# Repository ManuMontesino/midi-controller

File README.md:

# midi-controller

Controlador USB-MIDI + HID basado en RP2040: 8 encoders con anillo de LEDs, 8 teclas mecánicas con LED RGB, salida MIDI TRS y header de expansión.

> **Estado: Rev. 1, diseño terminado y listo para fabricar.** Pasa ERC y DRC sin errores, tiene archivos de producción para JLCPCB y la revisión de pinouts contra las hojas de datos está hecha. Todavía no se fabricó: el arranque de la placa (bring-up) y el firmware son los próximos pasos.

---

## Características

- **RP2040 como chip suelto** (no un módulo Pico): flash QSPI W25Q16 de 2 MB, cristal de 12 MHz, USB-C con protección ESD y polyfuse.
- **32 entradas** leídas con 4× 74HC165 en cadena: 8 encoders EC11 (A, B y pulsador) y 8 teclas MX.
- **144 LEDs** manejados por un IS31FL3741A por I2C: 8 anillos de 15 LEDs y 8 LEDs RGB debajo de las teclas, con PWM independiente para cada LED.
- **MIDI TRS (Type A)** a 3.3 V, además de USB-MIDI.
- **Header de expansión** con 6 GPIO, 3 entradas ADC, 3V3 y GND, para variantes sin rediseñar la placa base.
- **Debug:** header SWD y botones BOOTSEL y RESET.

## Hardware

```
USB-C ──► ESD + polyfuse ──► LDO 3.3V ──┬──► RP2040 + flash QSPI + cristal 12 MHz
                                        │       ├─ SPI ──► 4× 74HC165 ◄── 8 encoders + 8 teclas
                                        │       ├─ I2C ──► IS31FL3741A ──► 8 anillos + 8 RGB
                                        │       ├─ UART ─► jack TRS (MIDI out)
                                        │       └─ GPIO / ADC ──► header de expansión
                                        └──► +5V ──► alimentación de la matriz de LEDs
```

| | |
|---|---|
| Herramienta | KiCad 9, esquemático jerárquico de 6 hojas |
| PCB | 4 capas (señal / GND / 3V3 / señal), ~170 × 110 mm, 1.6 mm |
| Reglas | Pista y separación de 0.2 mm (0.15 mm en el fan-out del RP2040 y del IS31) |
| Componentes | 204 piezas SMD y THT ensamblables en JLCPCB (Economic PCBA, una sola cara) |
| Costo del prototipo | ~USD 150 por 5 PCB, 2 de ellas ensambladas, sin envío ni impuestos |

### Decisiones de diseño

Cada decisión está explicada en detalle en [las notas de diseño](docs/notas-de-diseno.md). Las principales:

- **Registros de desplazamiento en lugar de GPIO directos.** 32 entradas con solo 3 pines. Cada chip se agrupa por zona de la placa y no por tipo de señal, para acortar el ruteo.
- **Matriz de LEDs a 5 V con lógica a 3.3 V.** Un LED blanco (~3 V) más la caída del driver (hasta 1.35 V) necesita unos 4.35 V, así que a 3.3 V no prendería. Alimentarla desde 5 V además evita que la corriente de los LEDs pase por el LDO. El IS31 acepta lógica de 3.3 V, así que no hace falta convertir niveles.
- **USB-C hecho bien.** Una resistencia de 5.1k en cada pin CC, para que funcione con cables C-a-C. ESD con un USBLC6 de tipo "flow-through" pegado al conector y resistencias de 27 Ω en D+/D− junto al RP2040.
- **BOOTSEL sin pin dedicado.** El botón tira QSPI_SS a GND a través de 1k: la ROM lo lee al arrancar y el RP2040 todavía puede manejar la línea.
- **Estados seguros al arrancar.** SDB del IS31 tiene un pull-down, así que los LEDs quedan apagados hasta que el firmware los habilita.
- **Ruteo.** Desacoples pegados a cada pin de alimentación, par USB ruteado junto y plano de GND continuo en In1.

## Imágenes

| Vista superior | Cobre: F.Cu (rojo) y B.Cu (azul) |
|---|---|
|  |  |

| Plano In1 (GND) | Plano In2 (3V3) |
|---|---|
|  |  |

Esquemático completo: [docs/esquematico-rev1.pdf](docs/esquematico-rev1.pdf)

## Verificación

- **ERC:** 0 errores. **DRC:** 0 violaciones, 0 pads sin conectar y placa en paridad con el esquemático.
- **Revisión manual de pinouts contra las hojas de datos:** USB-C, USBLC6, AP2112K, RP2040 (alimentación, cristal y QSPI), W25Q16, 74HC165 e IS31FL3741A.
- **Disponibilidad de componentes en JLCPCB/LCSC:** las piezas sin stock se reemplazaron por equivalentes o se marcaron para soldar a mano.

## Fabricación

Los archivos de producción para JLCPCB están en [`hardware/midi-controller/fab/jlcpcb/`](hardware/midi-controller/fab/jlcpcb/): Gerbers y taladros en un zip, BOM con códigos LCSC y CPL de posiciones.

Se sueldan a mano: el jack MIDI (J2), las teclas MX, y los headers SWD y de expansión.

## Próximos pasos

1. **Bring-up:** medir los rieles de alimentación (hay test points en +5V, +3V3 y +1V1), comprobar que el RP2040 enumera en modo BOOTSEL y hacer un escaneo I2C (el IS31 debe responder en 0x30).
2. **Firmware** (Pico SDK + TinyUSB): lectura de entradas en el core 1, USB-MIDI/HID y LEDs en el core 0. Las notas para el firmware están en la sección 8 de [las notas de diseño](docs/notas-de-diseno.md).
3. **Configurador web** con Web MIDI y SysEx.

La especificación completa está en [`controlador-midi-spec.md`](controlador-midi-spec.md).

## Estructura

| Carpeta | Contenido |
|---|---|
| `hardware/midi-controller/` | Proyecto KiCad 9 (esquemático jerárquico + PCB de 4 capas) |
| `hardware/midi-controller/fab/jlcpcb/` | Gerbers, BOM y CPL para JLCPCB |
| `docs/` | Notas de diseño, esquemático en PDF e imágenes |
| `firmware/` | Firmware (por empezar) |
| `configurator/` | Configurador web (por empezar) |

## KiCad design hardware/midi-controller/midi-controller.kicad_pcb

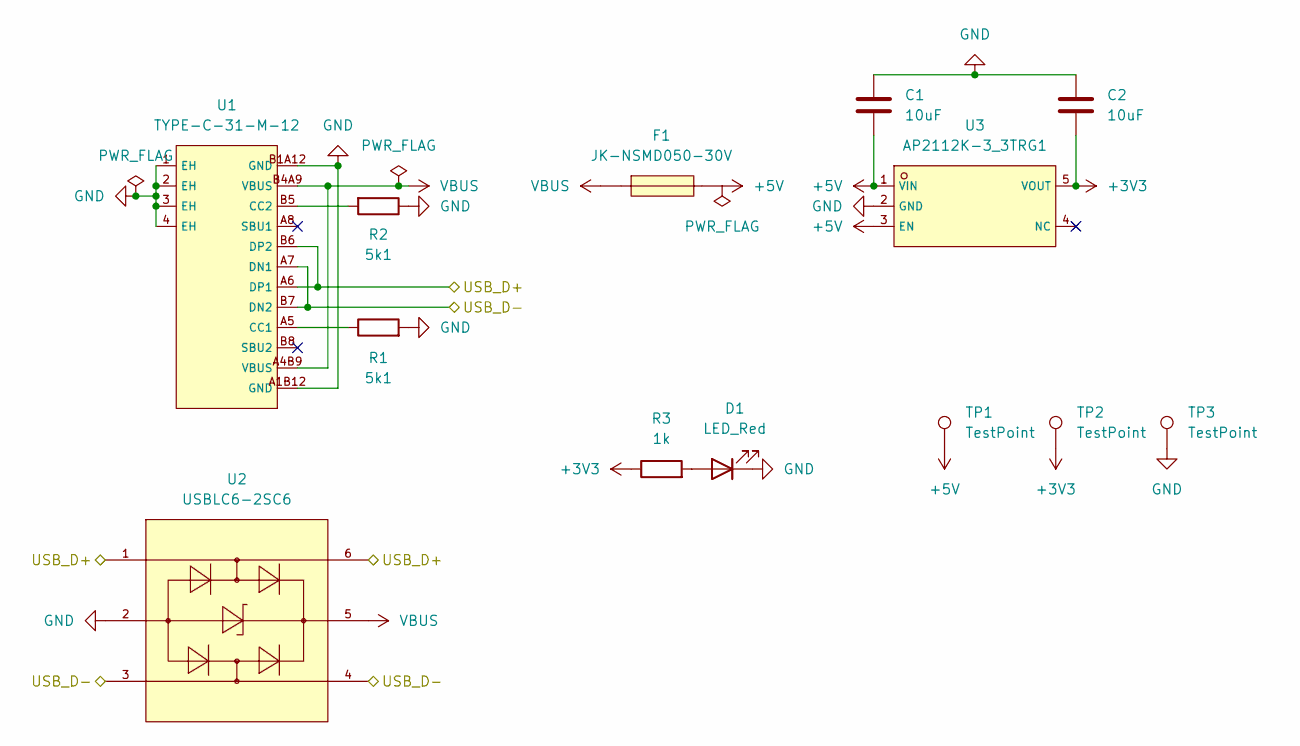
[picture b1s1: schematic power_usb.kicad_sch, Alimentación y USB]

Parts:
C1, C2: 10uF; C_0805_2012Metric; LCSC C15850
D1: LED_Red; LED_0603_1608Metric; LCSC C2286
F1: JK-NSMD050-30V; F1206; LCSC C720075
R1, R2: 5k1; R_0402_1005Metric; LCSC C25905
R3: 1k; R_0402_1005Metric; LCSC C11702
TP1, TP2, TP3: TestPoint; TestPoint_Pad_D1.5mm
U1: TYPE-C-31-M-12; USB-C_SMD-TYPE-C-31-M-12_1; LCSC C165948
U2: USBLC6-2SC6; SOT-23-6_L2.9-W1.6-P0.95-LS2.8-BL; LCSC C7519
U3: AP2112K-3_3TRG1; SOT-25-5_L2.9-W1.6-P0.95-LS2.8-BL; LCSC C51118

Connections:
+3V3: C2.2, R3.1, TP2.1, U3.5 (VOUT); also elsewhere on the board
+5V: C1.2, F1.2, TP1.1, U3.1 (VIN), U3.3 (EN); also elsewhere on the board
/Alimentación y USB/USB_D+: U1.A6 (DP1), U1.B6 (DP2), U2.1 (I/O1), U2.6 (I/O1); also elsewhere on the board
/Alimentación y USB/USB_D-: U1.A7 (DN1), U1.B7 (DN2), U2.3 (I/O2), U2.4 (I/O2); also elsewhere on the board
GND: C1.1, C2.1, D1.1 (K), R1.2, R2.1, TP3.1, U1.1 (EH), U1.2 (EH), U1.3 (EH), U1.4 (EH), U1.A1B12 (GND), U1.B1A12 (GND), U2.2 (GND), U3.2 (GND); also elsewhere on the board
unnamed: D1.2 (A), R3.2
unnamed: R1.1, U1.A5 (CC1)
unnamed: R2.2, U1.B5 (CC2)
VBUS: F1.1, U1.A4B9 (VBUS), U1.B4A9 (VBUS), U2.5 (VBUS)

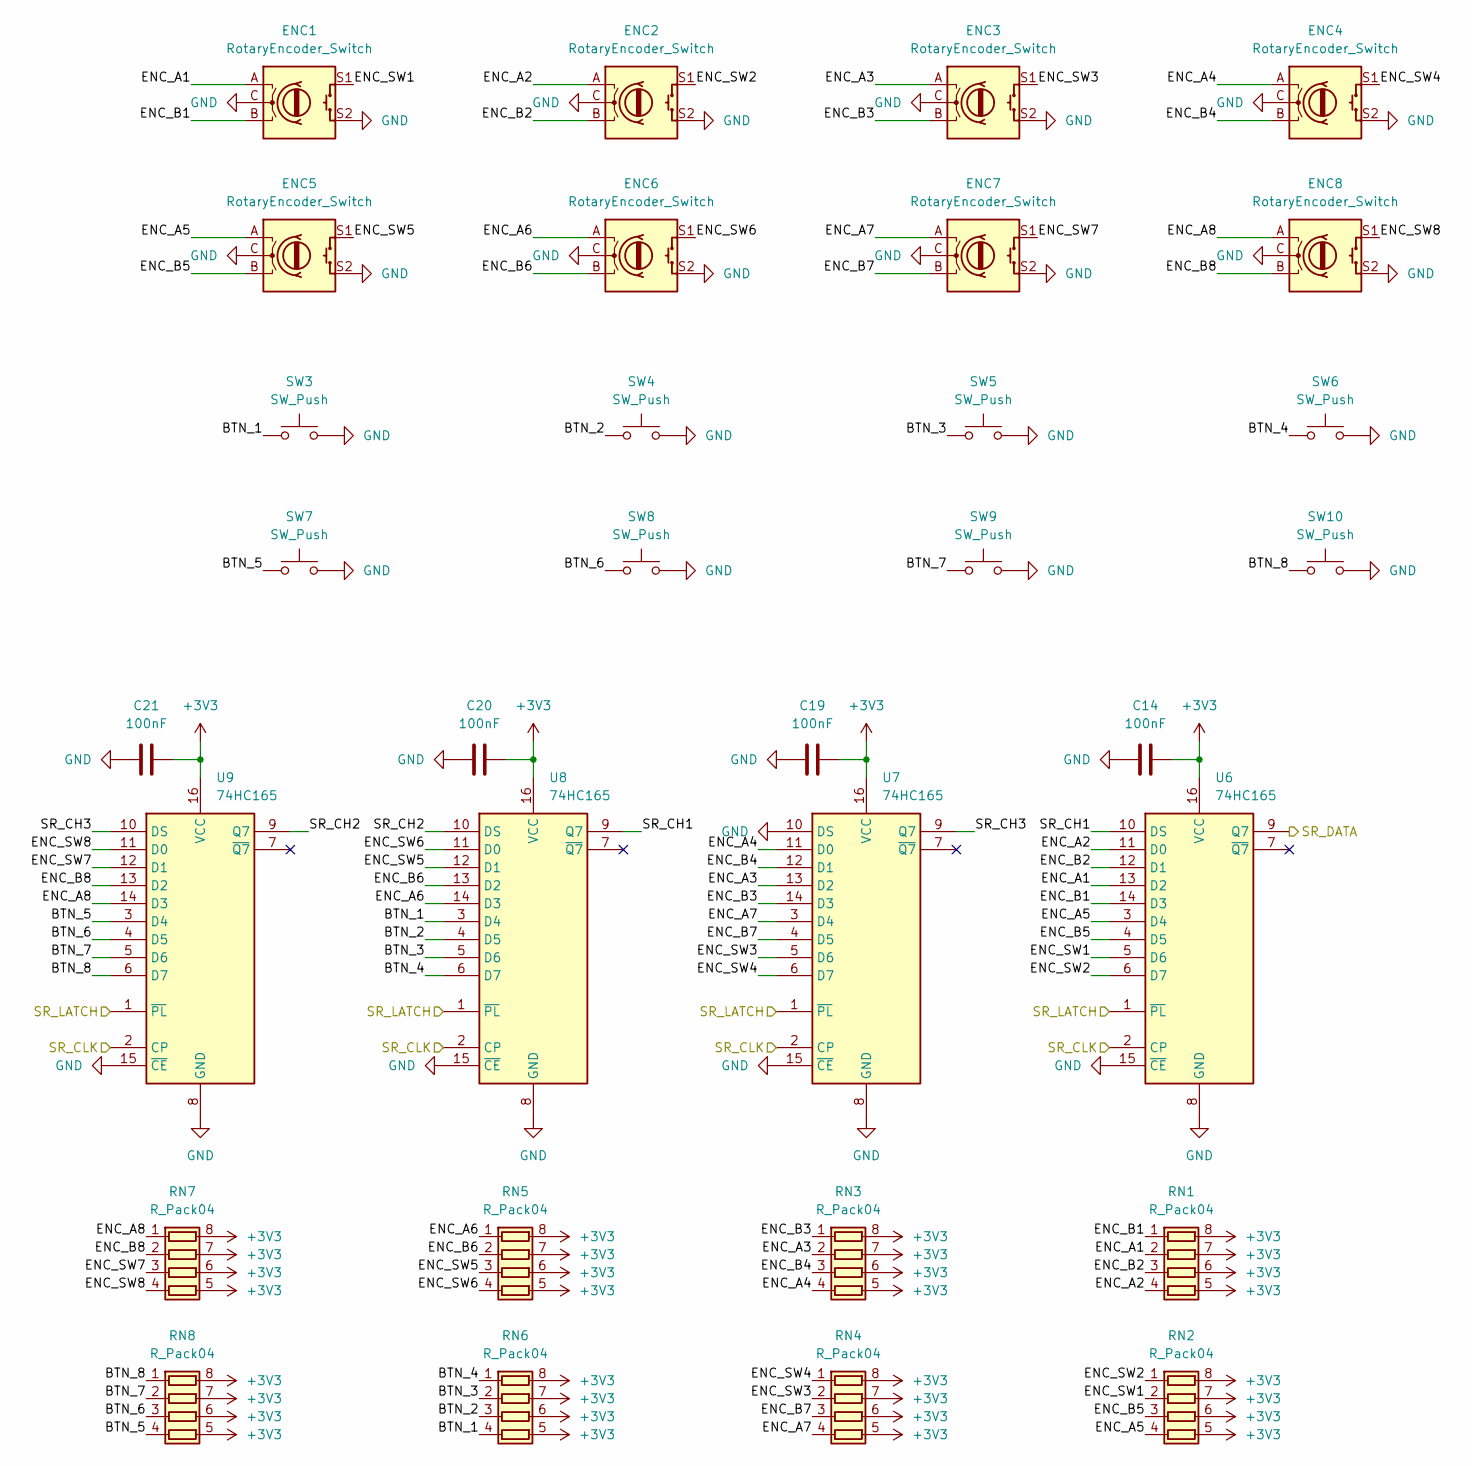
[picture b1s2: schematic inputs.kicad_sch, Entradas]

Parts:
C14, C19, C20, C21: 100nF; C_0402_1005Metric; LCSC C1525
ENC1, ENC2, ENC3, ENC4, ENC5, ENC6, ENC7, ENC8: RotaryEncoder_Switch; RotaryEncoder_Alps_EC11E-Switch_Vertical_H20mm; LCSC C255515
RN1, RN2, RN3, RN4, RN5, RN6, RN7, RN8: R_Pack04; R_Array_Convex_4x0603; LCSC C29718
SW3, SW4, SW5, SW6, SW7, SW8, SW9, SW10: SW_Push; SW_Cherry_MX_1.00u_PCB
U6, U7, U8, U9: 74HC165; SOIC-16_3.9x9.9mm_P1.27mm; LCSC C5613

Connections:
+3V3: C14.2, C19.2, C20.2, C21.2, RN1.5 (R4.2), RN1.6 (R3.2), RN1.7 (R2.2), RN1.8 (R1.2), RN2.5 (R4.2), RN2.6 (R3.2), RN2.7 (R2.2), RN2.8 (R1.2), RN3.5 (R4.2), RN3.6 (R3.2), RN3.7 (R2.2), RN3.8 (R1.2), RN4.5 (R4.2), RN4.6 (R3.2), RN4.7 (R2.2), RN4.8 (R1.2), RN5.5 (R4.2), RN5.6 (R3.2), RN5.7 (R2.2), RN5.8 (R1.2), RN6.5 (R4.2), RN6.6 (R3.2), RN6.7 (R2.2), RN6.8 (R1.2), RN7.5 (R4.2), RN7.6 (R3.2), RN7.7 (R2.2), RN7.8 (R1.2), RN8.5 (R4.2), RN8.6 (R3.2), RN8.7 (R2.2), RN8.8 (R1.2), U6.16 (VCC), U7.16 (VCC), U8.16 (VCC), U9.16 (VCC); also elsewhere on the board
/Entradas/BTN_1: RN6.4 (R4.1), SW3.1, U8.3 (D4)
/Entradas/BTN_2: RN6.3 (R3.1), SW4.1, U8.4 (D5)
/Entradas/BTN_3: RN6.2 (R2.1), SW5.1, U8.5 (D6)
/Entradas/BTN_4: RN6.1 (R1.1), SW6.1, U8.6 (D7)
/Entradas/BTN_5: RN8.4 (R4.1), SW7.1, U9.3 (D4)
/Entradas/BTN_6: RN8.3 (R3.1), SW8.1, U9.4 (D5)
/Entradas/BTN_7: RN8.2 (R2.1), SW9.1, U9.5 (D6)
/Entradas/BTN_8: RN8.1 (R1.1), SW10.1, U9.6 (D7)
/Entradas/ENC_A1: ENC1.A, RN1.2 (R2.1), U6.13 (D2)
/Entradas/ENC_A2: ENC2.A, RN1.4 (R4.1), U6.11 (D0)
/Entradas/ENC_A3: ENC3.A, RN3.2 (R2.1), U7.13 (D2)
/Entradas/ENC_A4: ENC4.A, RN3.4 (R4.1), U7.11 (D0)
/Entradas/ENC_A5: ENC5.A, RN2.4 (R4.1), U6.3 (D4)
/Entradas/ENC_A6: ENC6.A, RN5.1 (R1.1), U8.14 (D3)
/Entradas/ENC_A7: ENC7.A, RN4.4 (R4.1), U7.3 (D4)
/Entradas/ENC_A8: ENC8.A, RN7.1 (R1.1), U9.14 (D3)
/Entradas/ENC_B1: ENC1.B, RN1.1 (R1.1), U6.14 (D3)
/Entradas/ENC_B2: ENC2.B, RN1.3 (R3.1), U6.12 (D1)
/Entradas/ENC_B3: ENC3.B, RN3.1 (R1.1), U7.14 (D3)
/Entradas/ENC_B4: ENC4.B, RN3.3 (R3.1), U7.12 (D1)
/Entradas/ENC_B5: ENC5.B, RN2.3 (R3.1), U6.4 (D5)
/Entradas/ENC_B6: ENC6.B, RN5.2 (R2.1), U8.13 (D2)
/Entradas/ENC_B7: ENC7.B, RN4.3 (R3.1), U7.4 (D5)
/Entradas/ENC_B8: ENC8.B, RN7.2 (R2.1), U9.13 (D2)
/Entradas/ENC_SW1: ENC1.S1, RN2.2 (R2.1), U6.5 (D6)
/Entradas/ENC_SW2: ENC2.S1, RN2.1 (R1.1), U6.6 (D7)
/Entradas/ENC_SW3: ENC3.S1, RN4.2 (R2.1), U7.5 (D6)
/Entradas/ENC_SW4: ENC4.S1, RN4.1 (R1.1), U7.6 (D7)
/Entradas/ENC_SW5: ENC5.S1, RN5.3 (R3.1), U8.12 (D1)
/Entradas/ENC_SW6: ENC6.S1, RN5.4 (R4.1), U8.11 (D0)
/Entradas/ENC_SW7: ENC7.S1, RN7.3 (R3.1), U9.12 (D1)
/Entradas/ENC_SW8: ENC8.S1, RN7.4 (R4.1), U9.11 (D0)
/Entradas/SR_CH1: U6.10 (DS), U8.9 (Q7)
/Entradas/SR_CH2: U8.10 (DS), U9.9 (Q7)
/Entradas/SR_CH3: U7.9 (Q7), U9.10 (DS)
/Entradas/SR_CLK: U6.2 (CP), U7.2 (CP), U8.2 (CP), U9.2 (CP); also elsewhere on the board
/Entradas/SR_DATA: U6.9 (Q7); also elsewhere on the board
/Entradas/SR_LATCH: U6.1 (~PL), U7.1 (~PL), U8.1 (~PL), U9.1 (~PL); also elsewhere on the board
GND: C14.1, C19.1, C20.1, C21.1, ENC1.C, ENC1.S2, ENC2.C, ENC2.S2, ENC3.C, ENC3.S2, ENC4.C, ENC4.S2, ENC5.C, ENC5.S2, ENC6.C, ENC6.S2, ENC7.C, ENC7.S2, ENC8.C, ENC8.S2, SW3.2, SW4.2, SW5.2, SW6.2, SW7.2, SW8.2, SW9.2, SW10.2, U6.8 (GND), U6.15 (~CE), U7.8 (GND), U7.10 (DS), U7.15 (~CE), U8.8 (GND), U8.15 (~CE), U9.8 (GND), U9.15 (~CE); also elsewhere on the board

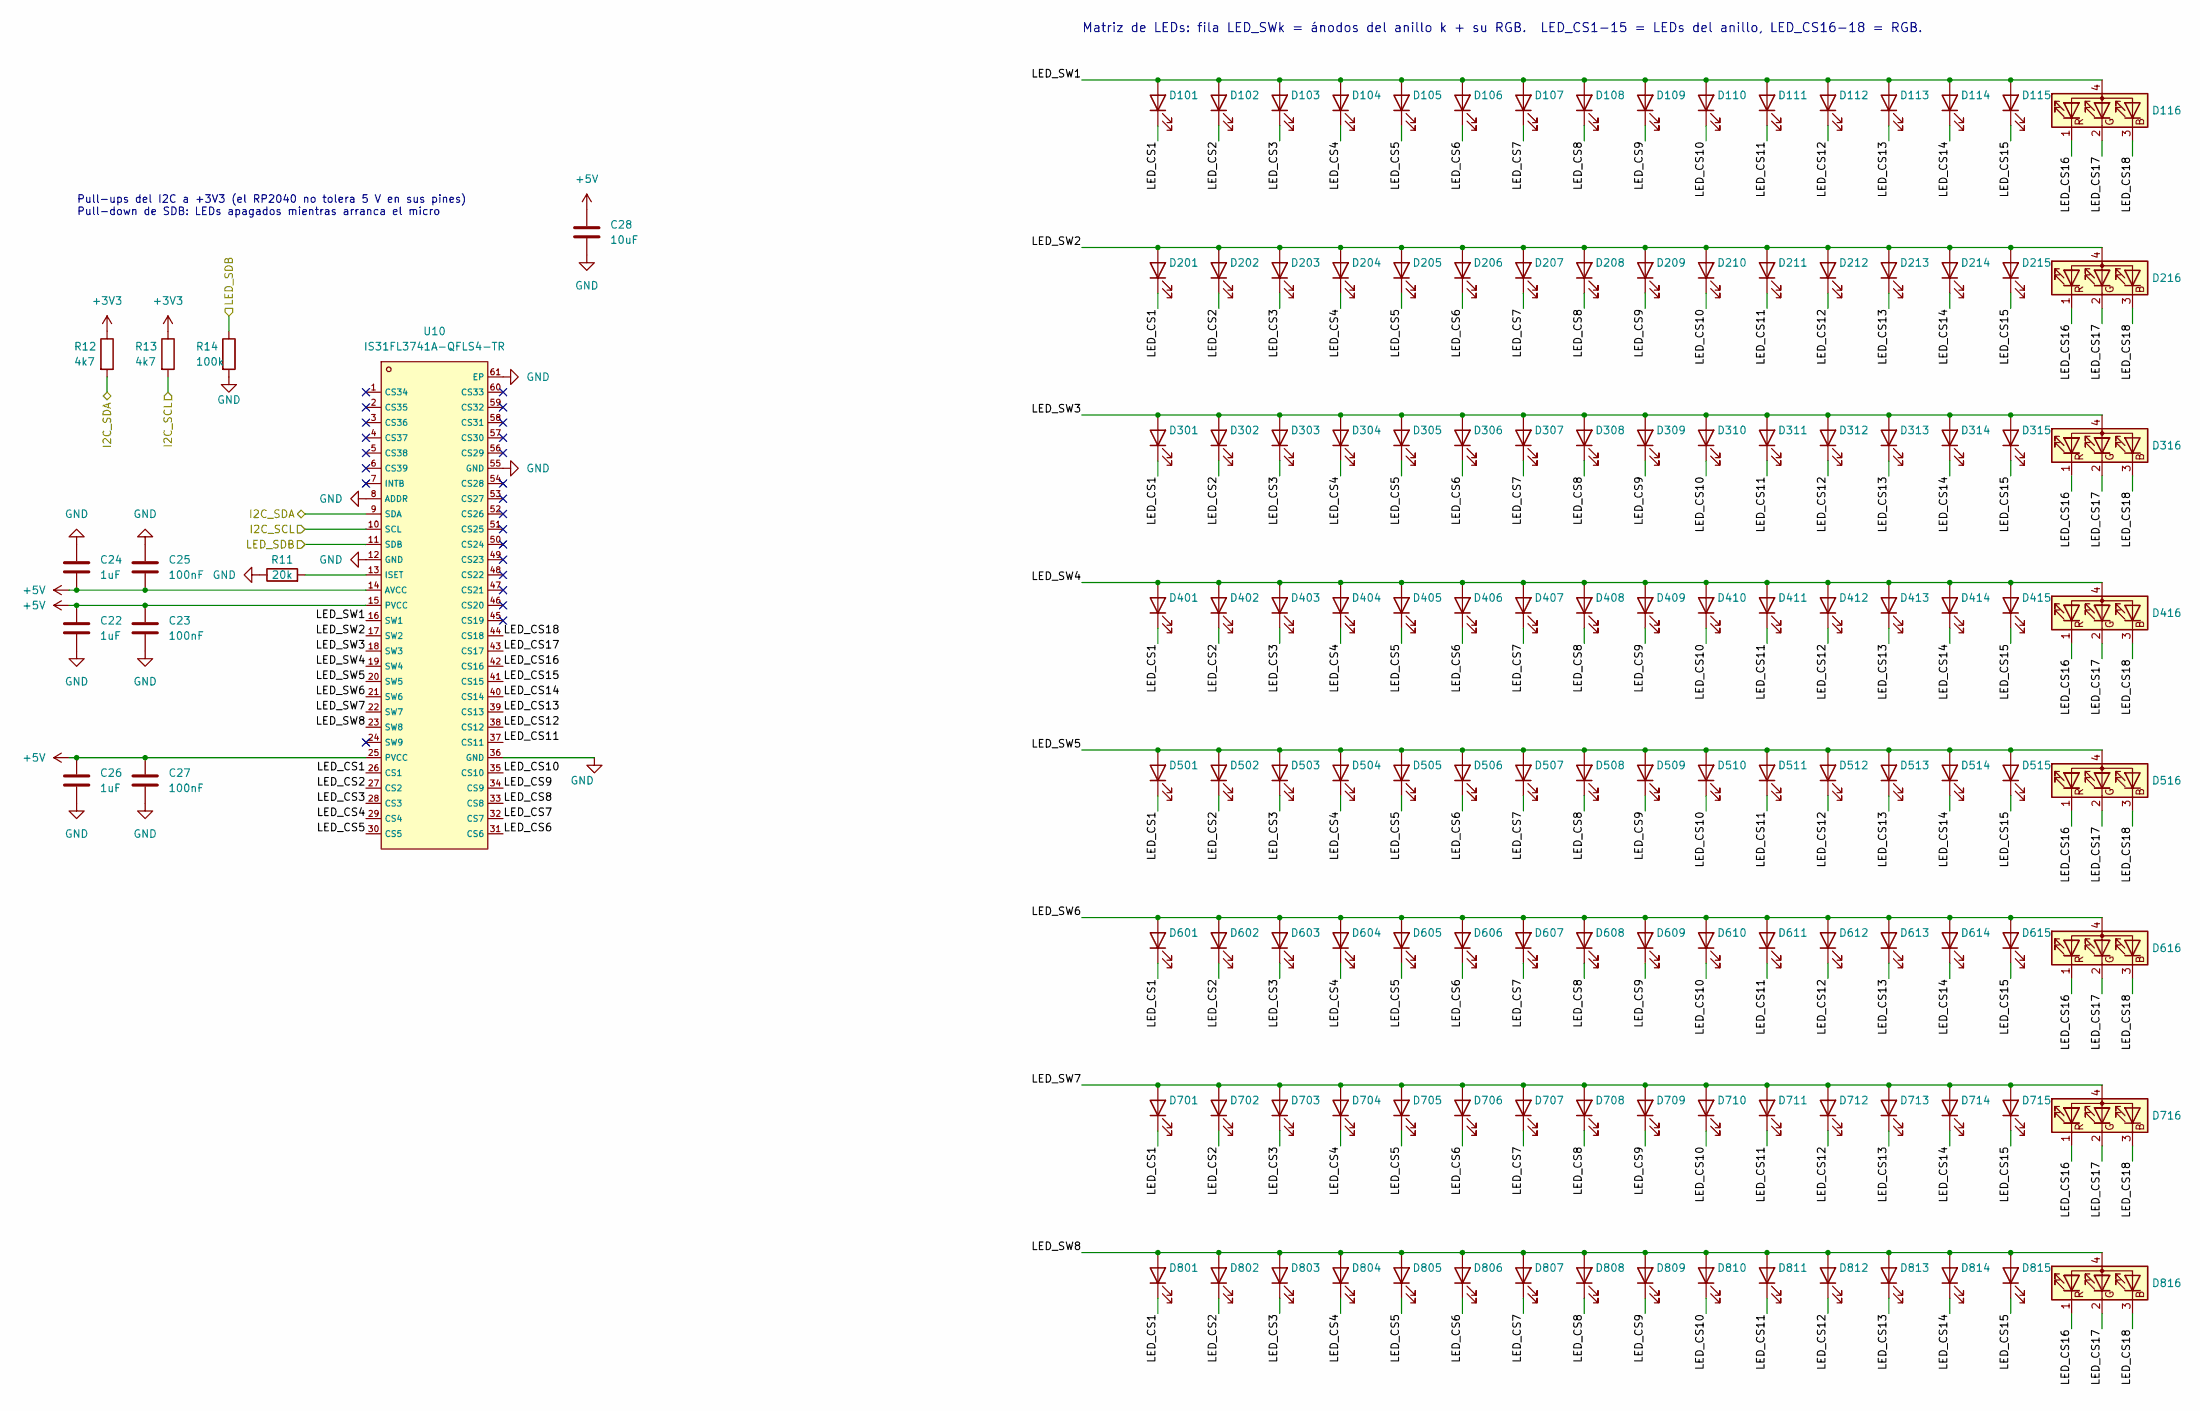
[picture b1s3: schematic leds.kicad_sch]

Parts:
C22, C24, C26: 1uF; C_0603_1608Metric; LCSC C15849
C23, C25, C27: 100nF; C_0402_1005Metric; LCSC C1525
C28: 10uF; C_0805_2012Metric; LCSC C15850
D101, D102, D103, D104, D105, D106, D107, D108, D109, D110, D111, D112, D113, D114, D115, D201, D202, D203, D204, D205, D206, D207, D208, D209, D210, D211, D212, D213, D214, D215, D301, D302, D303, D304, D305, D306, D307, D308, D309, D310, D311, D312, D313, D314, D315, D401, D402, D403, D404, D405, D406, D407, D408, D409, D410, D411, D412, D413, D414, D415, D501, D502, D503, D504, D505, D506, D507, D508, D509, D510, D511, D512, D513, D514, D515, D601, D602, D603, D604, D605, D606, D607, D608, D609, D610, D611, D612, D613, D614, D615, D701, D702, D703, D704, D705, D706, D707, D708, D709, D710, D711, D712, D713, D714, D715, D801, D802, D803, D804, D805, D806, D807, D808, D809, D810, D811, D812, D813, D814, D815: White; LED_0603_1608Metric; LCSC C2290
D116, D216, D316, D416, D516, D616, D716, D816: TJ-S3528 RGB; LED-ARRAY-SMD_4P-L3.2-W2.7-TL-RD_TJ-S3528; LCSC C601699
R11: 20k; R_0402_1005Metric; LCSC C25765
R12, R13: 4k7; R_0402_1005Metric; LCSC C25900
R14: 100k; R_0402_1005Metric; LCSC C25741
U10: IS31FL3741A-QFLS4-TR; QFN-60_L7.0-W7.0-P0.40-TL-EP5.3; LCSC C2940604

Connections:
+3V3: R12.1, R13.1; also elsewhere on the board
+5V: C22.1, C23.1, C24.2, C25.2, C26.1, C27.1, C28.1, U10.14 (AVCC), U10.15 (PVCC), U10.25 (PVCC); also elsewhere on the board
/LEDs/I2C_SCL: R13.2, U10.10 (SCL); also elsewhere on the board
/LEDs/I2C_SDA: R12.2, U10.9 (SDA); also elsewhere on the board
/LEDs/LED_CS1: D101.1 (K), D201.1 (K), D301.1 (K), D401.1 (K), D501.1 (K), D601.1 (K), D701.1 (K), D801.1 (K), U10.26 (CS1)
/LEDs/LED_CS2: D102.1 (K), D202.1 (K), D302.1 (K), D402.1 (K), D502.1 (K), D602.1 (K), D702.1 (K), D802.1 (K), U10.27 (CS2)
/LEDs/LED_CS3: D103.1 (K), D203.1 (K), D303.1 (K), D403.1 (K), D503.1 (K), D603.1 (K), D703.1 (K), D803.1 (K), U10.28 (CS3)
/LEDs/LED_CS4: D104.1 (K), D204.1 (K), D304.1 (K), D404.1 (K), D504.1 (K), D604.1 (K), D704.1 (K), D804.1 (K), U10.29 (CS4)
/LEDs/LED_CS5: D105.1 (K), D205.1 (K), D305.1 (K), D405.1 (K), D505.1 (K), D605.1 (K), D705.1 (K), D805.1 (K), U10.30 (CS5)
/LEDs/LED_CS6: D106.1 (K), D206.1 (K), D306.1 (K), D406.1 (K), D506.1 (K), D606.1 (K), D706.1 (K), D806.1 (K), U10.31 (CS6)
/LEDs/LED_CS7: D107.1 (K), D207.1 (K), D307.1 (K), D407.1 (K), D507.1 (K), D607.1 (K), D707.1 (K), D807.1 (K), U10.32 (CS7)
/LEDs/LED_CS8: D108.1 (K), D208.1 (K), D308.1 (K), D408.1 (K), D508.1 (K), D608.1 (K), D708.1 (K), D808.1 (K), U10.33 (CS8)
/LEDs/LED_CS9: D109.1 (K), D209.1 (K), D309.1 (K), D409.1 (K), D509.1 (K), D609.1 (K), D709.1 (K), D809.1 (K), U10.34 (CS9)
/LEDs/LED_CS10: D110.1 (K), D210.1 (K), D310.1 (K), D410.1 (K), D510.1 (K), D610.1 (K), D710.1 (K), D810.1 (K), U10.35 (CS10)
/LEDs/LED_CS11: D111.1 (K), D211.1 (K), D311.1 (K), D411.1 (K), D511.1 (K), D611.1 (K), D711.1 (K), D811.1 (K), U10.37 (CS11)
/LEDs/LED_CS12: D112.1 (K), D212.1 (K), D312.1 (K), D412.1 (K), D512.1 (K), D612.1 (K), D712.1 (K), D812.1 (K), U10.38 (CS12)
/LEDs/LED_CS13: D113.1 (K), D213.1 (K), D313.1 (K), D413.1 (K), D513.1 (K), D613.1 (K), D713.1 (K), D813.1 (K), U10.39 (CS13)
/LEDs/LED_CS14: D114.1 (K), D214.1 (K), D314.1 (K), D414.1 (K), D514.1 (K), D614.1 (K), D714.1 (K), D814.1 (K), U10.40 (CS14)
/LEDs/LED_CS15: D115.1 (K), D215.1 (K), D315.1 (K), D415.1 (K), D515.1 (K), D615.1 (K), D715.1 (K), D815.1 (K), U10.41 (CS15)
/LEDs/LED_CS16: D116.1 (RK), D216.1 (RK), D316.1 (RK), D416.1 (RK), D516.1 (RK), D616.1 (RK), D716.1 (RK), D816.1 (RK), U10.42 (CS16)
/LEDs/LED_CS17: D116.2 (GK), D216.2 (GK), D316.2 (GK), D416.2 (GK), D516.2 (GK), D616.2 (GK), D716.2 (GK), D816.2 (GK), U10.43 (CS17)
/LEDs/LED_CS18: D116.3 (BK), D216.3 (BK), D316.3 (BK), D416.3 (BK), D516.3 (BK), D616.3 (BK), D716.3 (BK), D816.3 (BK), U10.44 (CS18)
/LEDs/LED_SDB: R14.1, U10.11 (SDB); also elsewhere on the board
/LEDs/LED_SW1: D101.2 (A), D102.2 (A), D103.2 (A), D104.2 (A), D105.2 (A), D106.2 (A), D107.2 (A), D108.2 (A), D109.2 (A), D110.2 (A), D111.2 (A), D112.2 (A), D113.2 (A), D114.2 (A), D115.2 (A), D116.4 (A), U10.16 (SW1)
/LEDs/LED_SW2: D201.2 (A), D202.2 (A), D203.2 (A), D204.2 (A), D205.2 (A), D206.2 (A), D207.2 (A), D208.2 (A), D209.2 (A), D210.2 (A), D211.2 (A), D212.2 (A), D213.2 (A), D214.2 (A), D215.2 (A), D216.4 (A), U10.17 (SW2)
/LEDs/LED_SW3: D301.2 (A), D302.2 (A), D303.2 (A), D304.2 (A), D305.2 (A), D306.2 (A), D307.2 (A), D308.2 (A), D309.2 (A), D310.2 (A), D311.2 (A), D312.2 (A), D313.2 (A), D314.2 (A), D315.2 (A), D316.4 (A), U10.18 (SW3)
/LEDs/LED_SW4: D401.2 (A), D402.2 (A), D403.2 (A), D404.2 (A), D405.2 (A), D406.2 (A), D407.2 (A), D408.2 (A), D409.2 (A), D410.2 (A), D411.2 (A), D412.2 (A), D413.2 (A), D414.2 (A), D415.2 (A), D416.4 (A), U10.19 (SW4)
/LEDs/LED_SW5: D501.2 (A), D502.2 (A), D503.2 (A), D504.2 (A), D505.2 (A), D506.2 (A), D507.2 (A), D508.2 (A), D509.2 (A), D510.2 (A), D511.2 (A), D512.2 (A), D513.2 (A), D514.2 (A), D515.2 (A), D516.4 (A), U10.20 (SW5)
/LEDs/LED_SW6: D601.2 (A), D602.2 (A), D603.2 (A), D604.2 (A), D605.2 (A), D606.2 (A), D607.2 (A), D608.2 (A), D609.2 (A), D610.2 (A), D611.2 (A), D612.2 (A), D613.2 (A), D614.2 (A), D615.2 (A), D616.4 (A), U10.21 (SW6)
/LEDs/LED_SW7: D701.2 (A), D702.2 (A), D703.2 (A), D704.2 (A), D705.2 (A), D706.2 (A), D707.2 (A), D708.2 (A), D709.2 (A), D710.2 (A), D711.2 (A), D712.2 (A), D713.2 (A), D714.2 (A), D715.2 (A), D716.4 (A), U10.22 (SW7)
/LEDs/LED_SW8: D801.2 (A), D802.2 (A), D803.2 (A), D804.2 (A), D805.2 (A), D806.2 (A), D807.2 (A), D808.2 (A), D809.2 (A), D810.2 (A), D811.2 (A), D812.2 (A), D813.2 (A), D814.2 (A), D815.2 (A), D816.4 (A), U10.23 (SW8)
GND: C22.2, C23.2, C24.1, C25.1, C26.2, C27.2, C28.2, R11.1, R14.2, U10.8 (ADDR), U10.12 (GND), U10.36 (GND), U10.55 (GND), U10.61 (EP); also elsewhere on the board
unnamed: R11.2, U10.13 (ISET)

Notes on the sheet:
Pull-ups del I2C a +3V3 (el RP2040 no tolera 5 V en sus pines) Pull-down de SDB: LEDs apagados mientras arranca el micro
Matriz de LEDs: fila LED_SWk = ánodos del anillo k + su RGB. LED_CS1-15 = LEDs del anillo, LED_CS16-18 = RGB.

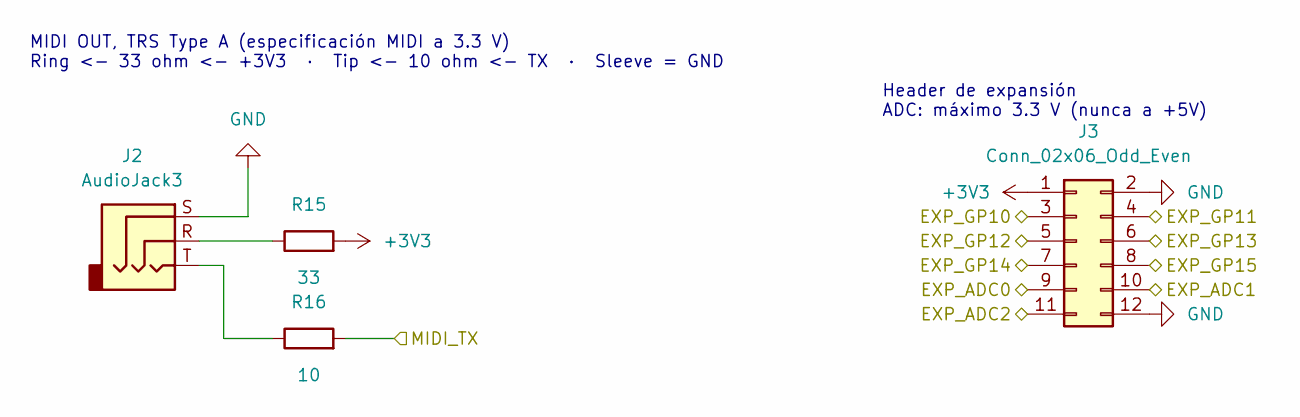
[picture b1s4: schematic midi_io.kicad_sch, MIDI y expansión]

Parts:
J2: AudioJack3; Jack_3.5mm_CUI_SJ1-3523N_Horizontal; LCSC C20182914
J3: Conn_02x06_Odd_Even; PinHeader_2x06_P2.54mm_Vertical
R15: 33; R_0402_1005Metric; LCSC C25105
R16: 10; R_0402_1005Metric; LCSC C25077

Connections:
+3V3: J3.1, R15.2; also elsewhere on the board
/MCU/EXP_ADC0: J3.9; also elsewhere on the board
/MCU/EXP_ADC1: J3.10; also elsewhere on the board
/MCU/EXP_ADC2: J3.11; also elsewhere on the board
/MCU/EXP_GP10: J3.3; also elsewhere on the board
/MCU/EXP_GP11: J3.4; also elsewhere on the board
/MCU/EXP_GP12: J3.5; also elsewhere on the board
/MCU/EXP_GP13: J3.6; also elsewhere on the board
/MCU/EXP_GP14: J3.7; also elsewhere on the board
/MCU/EXP_GP15: J3.8; also elsewhere on the board
/MCU/MIDI_TX: R16.2; also elsewhere on the board
GND: J2.S, J3.2, J3.12; also elsewhere on the board
unnamed: J2.R, R15.1
unnamed: J2.T, R16.1

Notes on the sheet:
MIDI OUT, TRS Type A (especificación MIDI a 3.3 V) Ring <- 33 ohm <- +3V3 · Tip <- 10 ohm <- TX · Sleeve = GND
Header de expansión ADC: máximo 3.3 V (nunca a +5V)

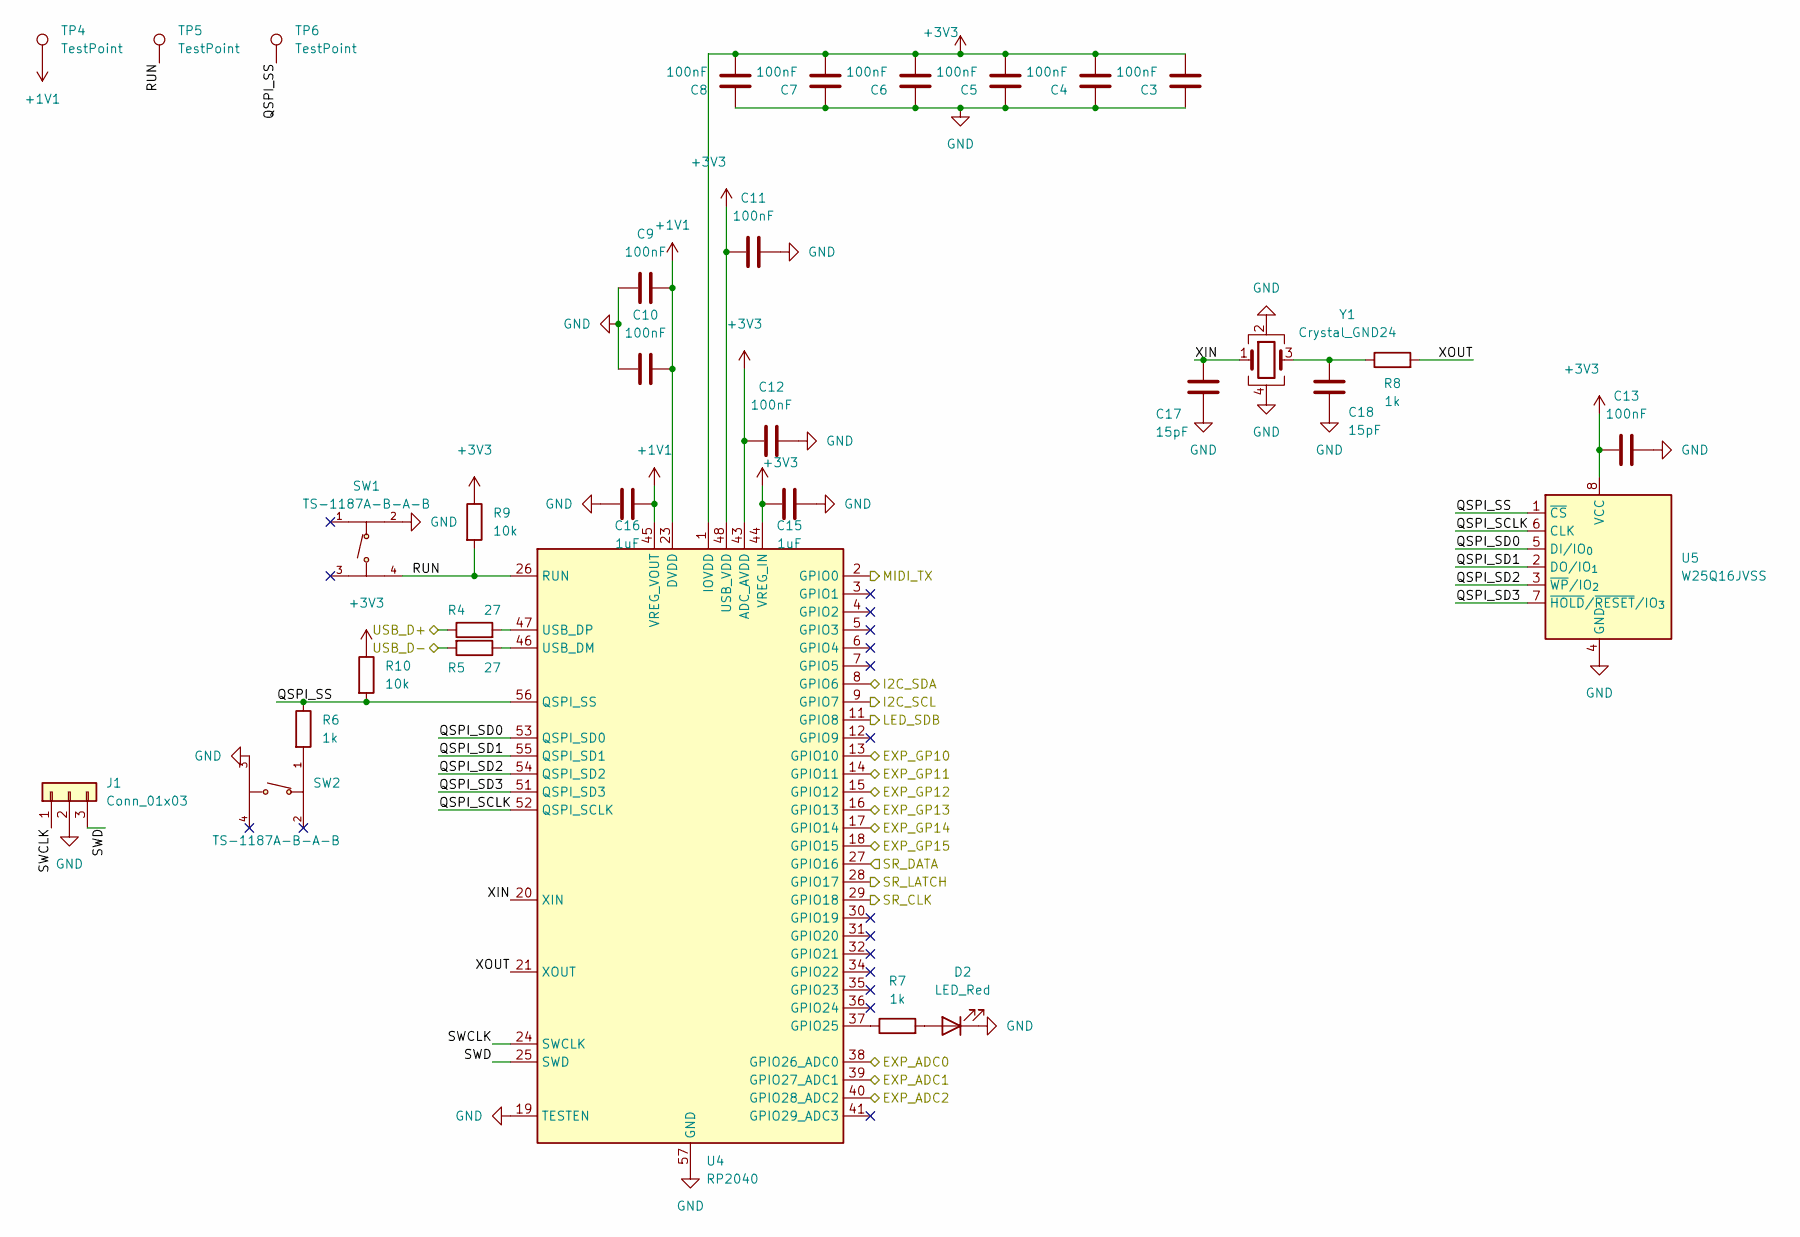
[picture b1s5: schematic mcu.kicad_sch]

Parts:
C3, C4, C5, C6, C7, C8, C9, C10, C11, C12, C13: 100nF; C_0402_1005Metric; LCSC C1525
C15, C16: 1uF; C_0402_1005Metric; LCSC C52923
C17, C18: 15pF; C_0402_1005Metric; LCSC C1548
D2: LED_Red; LED_0603_1608Metric; LCSC C2286
J1: Conn_01x03; PinHeader_1x03_P2.54mm_Vertical
R4, R5: 27; R_0402_1005Metric; LCSC C25100
R6, R7, R8: 1k; R_0402_1005Metric; LCSC C11702
R9, R10: 10k; R_0402_1005Metric; LCSC C25744
SW1, SW2: TS-1187A-B-A-B; SW-SMD_4P-L5.1-W5.1-P3.70-LS6.5-TL_H1.5; LCSC C318884
TP4, TP5, TP6: TestPoint; TestPoint_Pad_D1.5mm
U4: RP2040; QFN-56-1EP_7x7mm_P0.4mm_EP3.2x3.2mm; LCSC C2040
U5: W25Q16JVSS; SOIC-8_5.3x5.3mm_P1.27mm; LCSC C131025
Y1: Crystal_GND24; Crystal_SMD_3225-4Pin_3.2x2.5mm; LCSC C20625731

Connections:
+1V1: C9.2, C10.2, C16.2, TP4.1, U4.23 (DVDD), U4.45 (VREG_VOUT), U4.50 (DVDD)
+3V3: C3.1, C4.1, C5.1, C6.1, C7.1, C8.1, C11.1, C12.1, C13.1, C15.1, R9.1, R10.1, U4.1 (IOVDD), U4.10 (IOVDD), U4.22 (IOVDD), U4.33 (IOVDD), U4.42 (IOVDD), U4.43 (ADC_AVDD), U4.44 (VREG_IN), U4.48 (USB_VDD), U4.49 (IOVDD), U5.8 (VCC); also elsewhere on the board
/Alimentación y USB/USB_D+: R4.1; also elsewhere on the board
/Alimentación y USB/USB_D-: R5.2; also elsewhere on the board
/Entradas/SR_CLK: U4.29 (GPIO18); also elsewhere on the board
/Entradas/SR_DATA: U4.27 (GPIO16); also elsewhere on the board
/Entradas/SR_LATCH: U4.28 (GPIO17); also elsewhere on the board
/LEDs/I2C_SCL: U4.9 (GPIO7); also elsewhere on the board
/LEDs/I2C_SDA: U4.8 (GPIO6); also elsewhere on the board
/LEDs/LED_SDB: U4.11 (GPIO8); also elsewhere on the board
/MCU/EXP_ADC0: U4.38 (GPIO26_ADC0); also elsewhere on the board
/MCU/EXP_ADC1: U4.39 (GPIO27_ADC1); also elsewhere on the board
/MCU/EXP_ADC2: U4.40 (GPIO28_ADC2); also elsewhere on the board
/MCU/EXP_GP10: U4.13 (GPIO10); also elsewhere on the board
/MCU/EXP_GP11: U4.14 (GPIO11); also elsewhere on the board
/MCU/EXP_GP12: U4.15 (GPIO12); also elsewhere on the board
/MCU/EXP_GP13: U4.16 (GPIO13); also elsewhere on the board
/MCU/EXP_GP14: U4.17 (GPIO14); also elsewhere on the board
/MCU/EXP_GP15: U4.18 (GPIO15); also elsewhere on the board
/MCU/MIDI_TX: U4.2 (GPIO0); also elsewhere on the board
/MCU/QSPI_SCLK: U4.52 (QSPI_SCLK), U5.6 (CLK)
/MCU/QSPI_SD0: U4.53 (QSPI_SD0), U5.5 (DI/IO_{0})
/MCU/QSPI_SD1: U4.55 (QSPI_SD1), U5.2 (DO/IO_{1})
/MCU/QSPI_SD2: U4.54 (QSPI_SD2), U5.3 (~WP/IO_{2})
/MCU/QSPI_SD3: U4.51 (QSPI_SD3), U5.7 (~HOLD/~RESET/IO_{3})
/MCU/QSPI_SS: R6.1, R10.2, TP6.1, U4.56 (QSPI_SS), U5.1 (~CS)
/MCU/RUN: R9.2, SW1.4 (D), TP5.1, U4.26 (RUN)
/MCU/SWCLK: J1.1, U4.24 (SWCLK)
/MCU/SWD: J1.3, U4.25 (SWD)
/MCU/XIN: C17.1, U4.20 (XIN), Y1.1
/MCU/XOUT: R8.2, U4.21 (XOUT)
GND: C3.2, C4.2, C5.2, C6.2, C7.2, C8.2, C9.1, C10.1, C11.2, C12.2, C13.2, C15.2, C16.1, C17.2, C18.2, D2.1 (K), J1.2, SW1.2 (B), SW2.3 (C), U4.19 (TESTEN), U4.57 (GND), U5.4 (GND), Y1.2, Y1.4; also elsewhere on the board
unnamed: C18.1, R8.1, Y1.3
unnamed: D2.2 (A), R7.2
unnamed: R6.2, SW2.1 (A)
unnamed: R7.1, U4.37 (GPIO25)
unnamed: R5.1, U4.46 (USB_DM)
unnamed: R4.2, U4.47 (USB_DP)

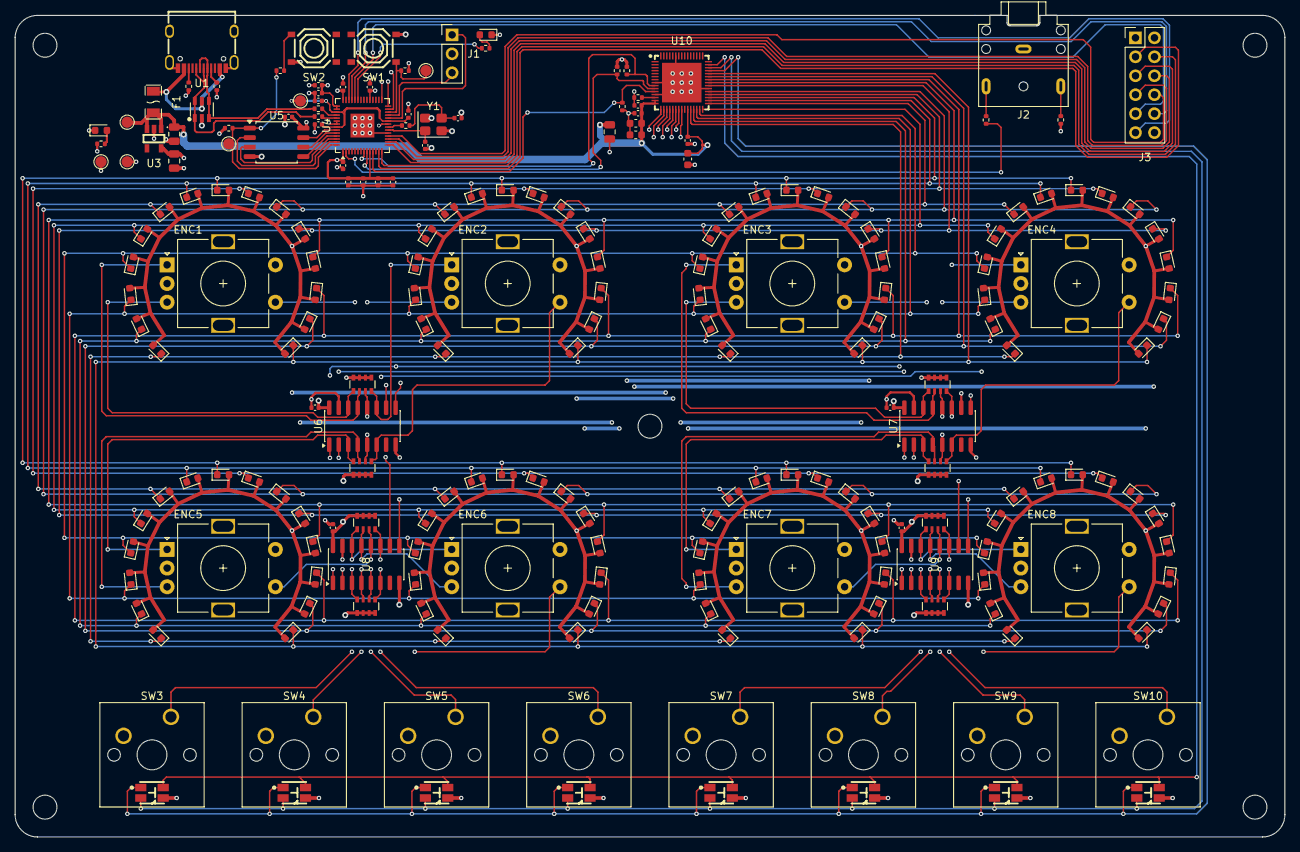
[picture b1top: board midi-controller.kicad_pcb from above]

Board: 4 copper layers, 170.0 x 110.0 mm, 226 parts (0 on the bottom side), 107 nets.

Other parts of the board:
H1, H2, H3, H4, H5: MountingHole_3.2mm_M3

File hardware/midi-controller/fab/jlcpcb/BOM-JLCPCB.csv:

Comment,Designator,Footprint,LCSC Part #
10uF,"C1,C2,C28",C_0805_2012Metric,C15850
100nF,"C3,C4,C5,C6,C7,C8,C9,C10,C11,C12,C13,C14,C19,C20,C21,C23,C25,C27",C_0402_1005Metric,C1525
1uF,"C15,C16",C_0402_1005Metric,C52923
15pF,"C17,C18",C_0402_1005Metric,C1548
1uF,"C22,C24,C26",C_0603_1608Metric,C15849
LED_Red,"D1,D2",LED_0603_1608Metric,C2286
White,"D101,D102,D103,D104,D105,D106,D107,D108,D109,D110,D111,D112,D113,D114,D115,D201,D202,D203,D204,D205,D206,D207,D208,D209,D210,D211,D212,D213,D214,D215,D301,D302,D303,D304,D305,D306,D307,D308,D309,D310,D311,D312,D313,D314,D315,D401,D402,D403,D404,D405,D406,D407,D408,D409,D410,D411,D412,D413,D414,D415,D501,D502,D503,D504,D505,D506,D507,D508,D509,D510,D511,D512,D513,D514,D515,D601,D602,D603,D604,D605,D606,D607,D608,D609,D610,D611,D612,D613,D614,D615,D701,D702,D703,D704,D705,D706,D707,D708,D709,D710,D711,D712,D713,D714,D715,D801,D802,D803,D804,D805,D806,D807,D808,D809,D810,D811,D812,D813,D814,D815",LED_0603_1608Metric,C2290
TJ-S3528 RGB,"D116,D216,D316,D416,D516,D616,D716,D816",LED-ARRAY-SMD_4P-L3.2-W2.7-TL-RD_TJ-S3528,C601699
RotaryEncoder_Switch,"ENC1,ENC2,ENC3,ENC4,ENC5,ENC6,ENC7,ENC8",RotaryEncoder_Alps_EC11E-Switch_Vertical_H20mm,C255515
JK-NSMD050-30V,F1,F1206,C720075
5k1,"R1,R2",R_0402_1005Metric,C25905
1k,"R3,R6,R7,R8",R_0402_1005Metric,C11702
27,"R4,R5",R_0402_1005Metric,C25100
10k,"R9,R10",R_0402_1005Metric,C25744
20k,R11,R_0402_1005Metric,C25765
4k7,"R12,R13",R_0402_1005Metric,C25900
100k,R14,R_0402_1005Metric,C25741
33,R15,R_0402_1005Metric,C25105
10,R16,R_0402_1005Metric,C25077
R_Pack04,"RN1,RN2,RN3,RN4,RN5,RN6,RN7,RN8",R_Array_Convex_4x0603,C29718
TS-1187A-B-A-B,"SW1,SW2",SW-SMD_4P-L5.1-W5.1-P3.70-LS6.5-TL_H1.5,C318884
TYPE-C-31-M-12,U1,USB-C_SMD-TYPE-C-31-M-12_1,C165948
USBLC6-2SC6,U2,SOT-23-6_L2.9-W1.6-P0.95-LS2.8-BL,C7519
AP2112K-3_3TRG1,U3,SOT-25-5_L2.9-W1.6-P0.95-LS2.8-BL,C51118
RP2040,U4,QFN-56-1EP_7x7mm_P0.4mm_EP3.2x3.2mm,C2040
W25Q16JVSS,U5,SOIC-8_5.3x5.3mm_P1.27mm,C131025
74HC165,"U6,U7,U8,U9",SOIC-16_3.9x9.9mm_P1.27mm,C5613
IS31FL3741A-QFLS4-TR,U10,QFN-60_L7.0-W7.0-P0.40-TL-EP5.3,C2940604
Crystal_GND24,Y1,Crystal_SMD_3225-4Pin_3.2x2.5mm,C20625731
